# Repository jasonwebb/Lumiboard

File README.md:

## Lumiboard

Lumiboard is an open-source platform for controlling many types of LEDs. An external sensor board enables tons of fun interactivity, and an on-board Bluetooth transceiver let's you control everything via smartphone or tablet. Lumiboard can control all of these types of LEDs:

* Discrete LEDs
* High-power common-cathode RGB (or single-color) LEDs, up to 5W
* Basic LED strips
* Digitally-addressable LED arrays (such as NeoPixel-based packages)
* I2C LED pixels (like the BlinkM)

## Board features
* **ATMega328** with the Arduino Pro Mini (8 mHz @ 3.3V) bootloader flashed
* **Screw terminals** allow all board functions to be easily tapped into.
* **Six PWM pins** broken out and connected through a ULN2003, so you can sink two high-power RGB LEDs.
* **I2C interface** (SDA and SCL pins) for programmable LEDs like the BlinkM. 
* **Three potentiometer inputs** so you can control RGB colors directly, or connect other sensors as analog inputs.
* **External sensor board** containing a temperature sensor, ambient light sensor and sound sensor.
* **Bluetooth transceiver** accessible via SoftwareSerial, so you can easily control your LEDs remotely using your smartphone or tablet.
* **FTDI interface (3.3V)** so you can re-program the board at any time manually.

## More information
* Author website: http://jason-webb.info
* All my blog posts about this project: http://jason-webb.info/tag/lumiboard/
* Wiki: http://jason-webb.info/wiki/index.php?title=Lumiboard

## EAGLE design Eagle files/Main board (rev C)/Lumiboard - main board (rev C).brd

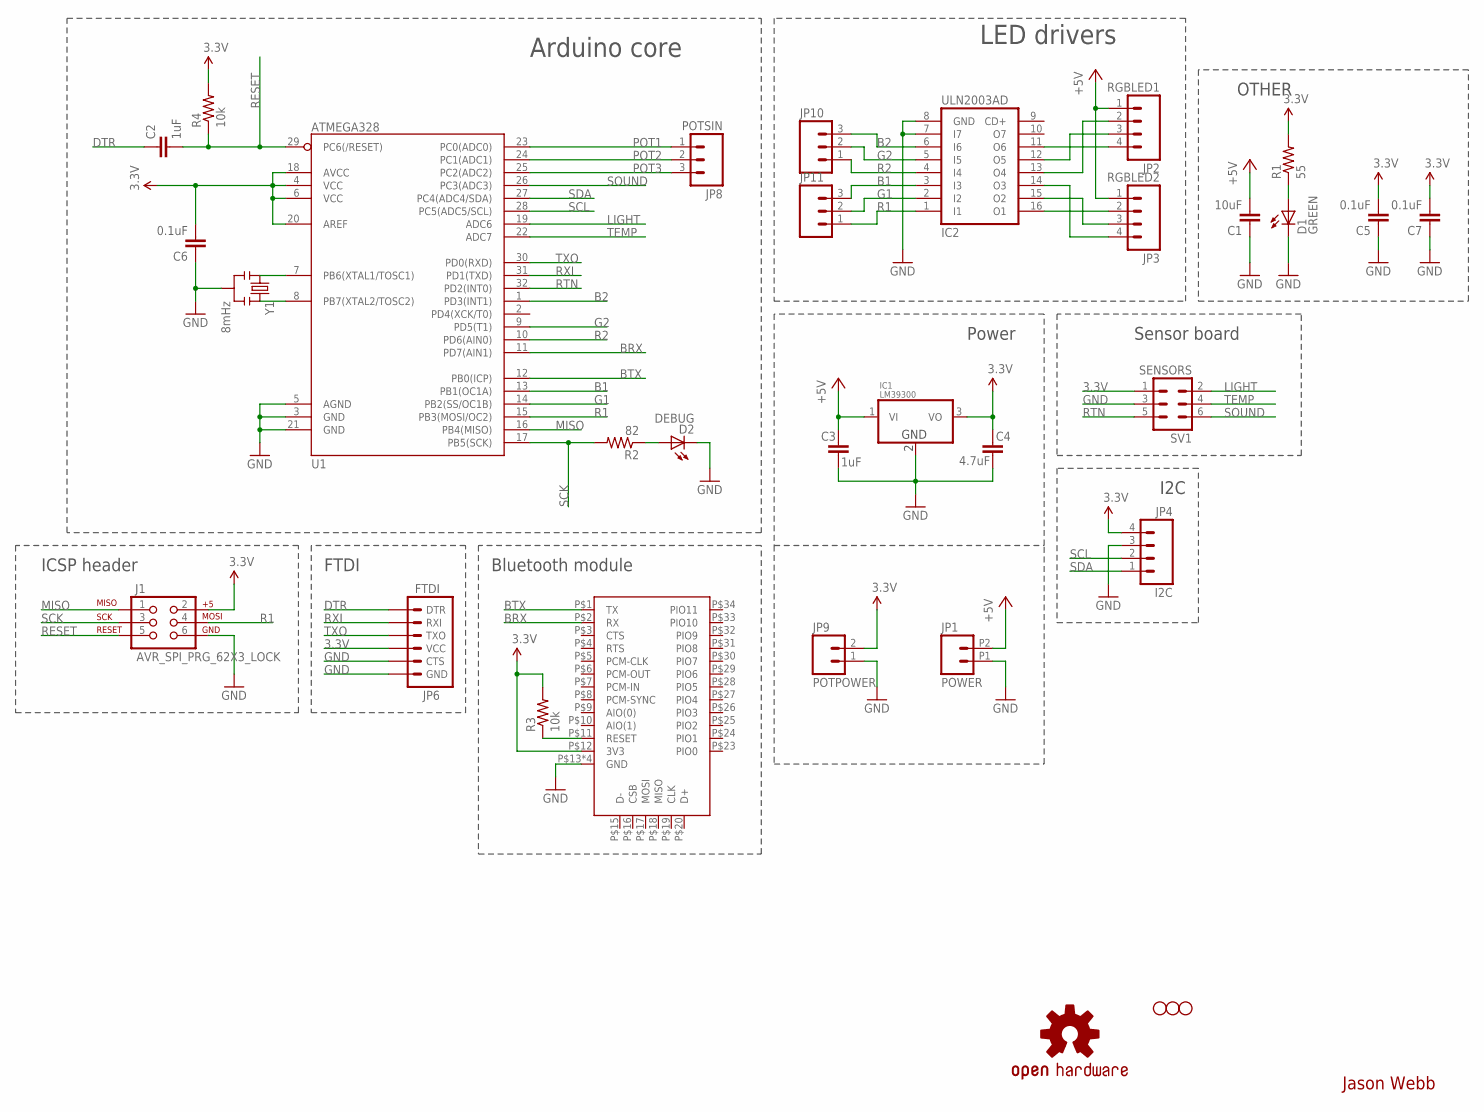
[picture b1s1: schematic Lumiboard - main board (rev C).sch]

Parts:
C1: 10uF; 0805
C2, C3: 1uF; 0805
C4: 4.7uF; 0805
C5, C6, C7: 0.1uF; 0805
D1: GREEN; CHIPLED_0805
D2: DEBUG; CHIPLED_0805
H1, H2, H3: STAND-OFFTIGHT; STAND-OFF-TIGHT
IC1: LM39300; DPAK
IC2: ULN2003AD; SO16
J1: AVR_SPI_PRG_62X3_LOCK; 2X3_LOCK
JP1: POWER; 1X02_2.54_SCREWTERM
JP2: RGBLED1; 1X04
JP3: RGBLED2; 1X04
JP4: I2C; 1X04
JP6: FTDI; 1X06_LOCK
JP8: POTSIN; 1X03
JP9: POTPOWER; 1X02
JP10, JP11: M03PTH; 1X03
LOGO1: OSHW-LOGOS; OSHW-LOGO-S
R1: 55; 0805
R2: 82; 0805
R3, R4: 10k; 0805
SV1: SENSORS; ML6
U1: ATMEGA328; TQFP32-08
U2: DX_BT_MODULE; DXBLUETOOTHMODULE
Y1: 8mHz; RESONATOR-SMD

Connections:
3.3V: C4.2, C5.2, C6.2, C7.2, IC1.3 (VO), J1.2, JP4.4, JP6.4 (VCC), JP9.2, R1.2, R3.2, R4.2, SV1.1, U1.4 (VCC), U1.6 (VCC), U1.18 (AVCC), U1.20 (AREF), U2.P$12 (3V3)
+5V: C1.2, C3.2, IC1.1 (VI), JP1.P2 (2), JP2.1, JP3.1
B1: IC2.3 (I3), JP11.3, U1.13 (PB1(OC1A))
B2: IC2.6 (I6), JP10.3, U1.1 (PD3(INT1))
BRX: U1.11 (PD7(AIN1)), U2.P$2 (RX)
BTRESET: R3.1, U2.P$11 (RESET)
BTX: U1.12 (PB0(ICP)), U2.P$1 (TX)
DTR: C2.1, JP6.1 (DTR)
G1: IC2.2 (I2), JP11.2, U1.14 (PB2(SS/OC1B))
G2: IC2.5 (I5), JP10.2, U1.9 (PD5(T1))
GND: C1.1, C3.1, C4.1, C5.1, C6.1, C7.1, D1.C, D2.C, IC1.2 (GND), IC2.7 (I7), IC2.8 (GND), J1.6, JP1.P1 (1), JP4.3, JP6.5 (CTS), JP6.6 (GND), JP9.1, SV1.3, U1.3 (GND), U1.5 (AGND), U1.21 (GND), U2.P$13 (GND), U2.P$14 (GND), U2.P$21 (GND), U2.P$22 (GND), Y1.2
LIGHT: SV1.2, U1.19 (ADC6)
MISO: J1.1, U1.16 (PB4(MISO))
unnamed: IC2.16 (O1), JP3.2
unnamed: IC2.15 (O2), JP3.3
unnamed: IC2.13 (O4), JP2.2
unnamed: IC2.14 (O3), JP3.4
unnamed: IC2.12 (O5), JP2.3
unnamed: U1.7 (PB6(XTAL1/TOSC1)), Y1.1
unnamed: U1.8 (PB7(XTAL2/TOSC2)), Y1.3
unnamed: D1.A, R1.1
unnamed: IC2.11 (O6), JP2.4
unnamed: D2.A, R2.1
POT1: JP8.1, U1.23 (PC0(ADC0))
POT2: JP8.2, U1.24 (PC1(ADC1))
POT3: JP8.3, U1.25 (PC2(ADC2))
R1: IC2.1 (I1), J1.4, JP11.1, U1.15 (PB3(MOSI/OC2))
R2: IC2.4 (I4), JP10.1, U1.10 (PD6(AIN0))
RESET: C2.2, J1.5, R4.1, U1.29 (PC6(/RESET))
RTN: SV1.5, U1.32 (PD2(INT0))
RXI: JP6.2 (RXI), U1.31 (PD1(TXD))
SCK: J1.3, R2.2, U1.17 (PB5(SCK))
SCL: JP4.2, U1.28 (PC5(ADC5/SCL))
SDA: JP4.1, U1.27 (PC4(ADC4/SDA))
SOUND: SV1.6, U1.26 (PC3(ADC3))
TEMP: SV1.4, U1.22 (ADC7)
TXO: JP6.3 (TXO), U1.30 (PD0(RXD))

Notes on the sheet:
Jason Webb
Arduino core
Bluetooth module
Sensor board
LED drivers
Power
FTDI
I2C
OTHER
ICSP header

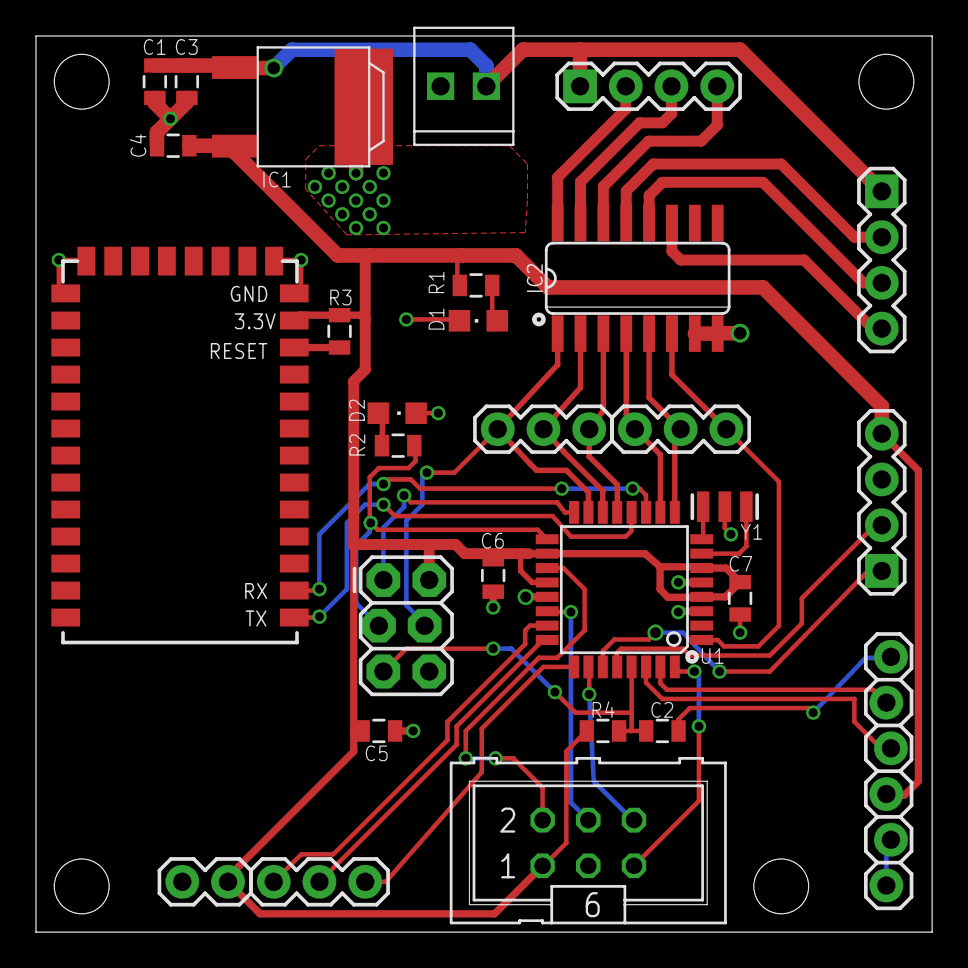
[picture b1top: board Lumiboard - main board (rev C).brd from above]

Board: 4 copper layers, 49.8 x 49.8 mm, 34 parts (1 on the bottom side), 37 nets.

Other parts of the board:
H4: STAND-OFFTIGHT; STAND-OFF-TIGHT

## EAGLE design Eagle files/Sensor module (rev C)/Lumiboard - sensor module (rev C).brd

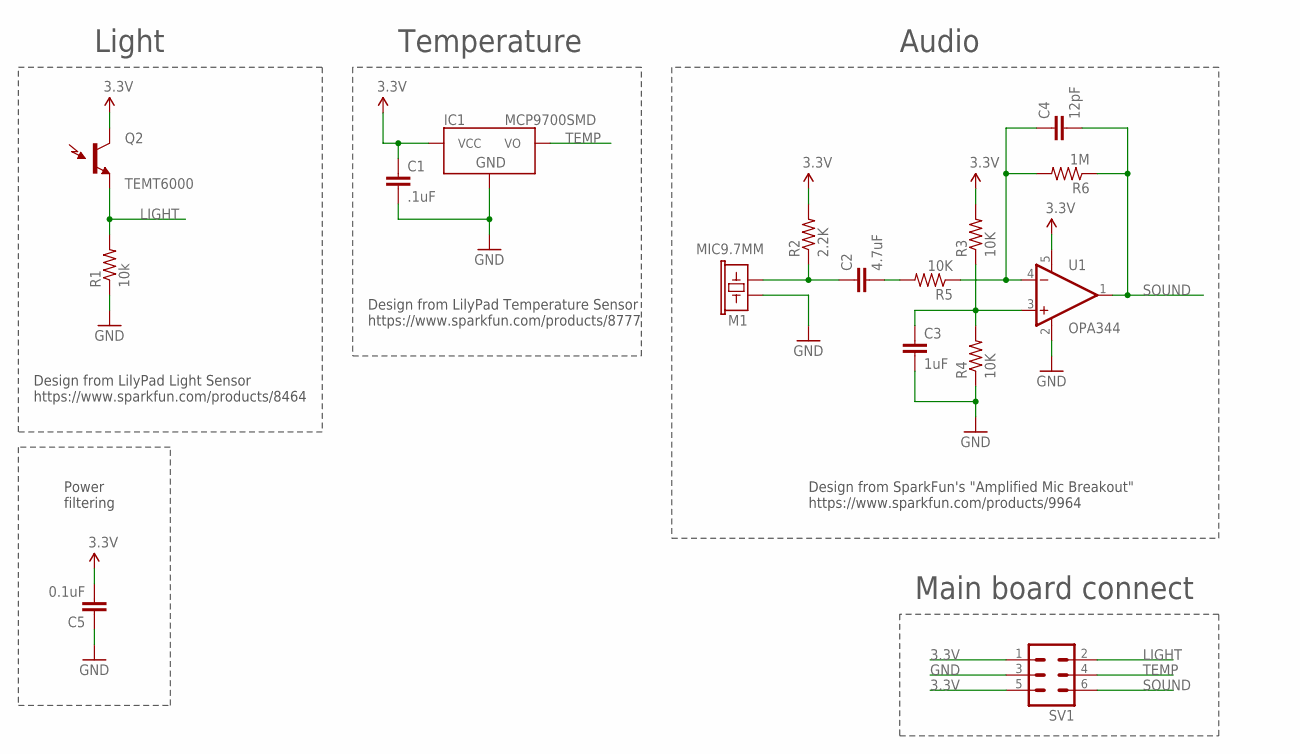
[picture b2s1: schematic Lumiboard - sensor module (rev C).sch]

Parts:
C1: .1uF; 0805
C2: 4.7uF; 0805
C3: 1uF; 0805
C4: 12pF; 0805
C5: 0.1uF; 0805
IC1: MCP9700SMD; SOT23-3
M1: MIC9.7MM; MIC-9.7MM
Q2: TEMT6000; TEMT6000-SEN
R1: 10k; 0805
R2: 2.2K; 0805
R3, R4, R5: 10K; 0805
R6: 1M; 0805
SV1: ML6
U1: OPA344; SOT23-5

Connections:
3.3V: C1.1, C5.2, IC1.1 (VCC), Q2.COLLECTOR (C1), R2.2, R3.2, SV1.1, SV1.5, U1.5 (V+)
GND: C1.2, C3.2, C5.1, IC1.3 (GND), M1.2, R1.1, R4.1, SV1.3, U1.2 (V-)
LIGHT: Q2.EMITTER (E1), R1.2, SV1.2
unnamed: C2.1, M1.1, R2.1
unnamed: C4.1, R5.1, R6.2, U1.4 (-IN)
unnamed: C2.2, R5.2
unnamed: C3.1, R3.1, R4.2, U1.3 (+IN)
SOUND: C4.2, R6.1, SV1.6, U1.1 (OUT)
TEMP: IC1.2 (VO), SV1.4

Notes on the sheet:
Light
Temperature
Main board connect
Audio
Design from SparkFun's "Amplified Mic Breakout" https://www.sparkfun.com/products/9964
Design from LilyPad Temperature Sensor https://www.sparkfun.com/products/8777
Design from LilyPad Light Sensor https://www.sparkfun.com/products/8464
Power filtering

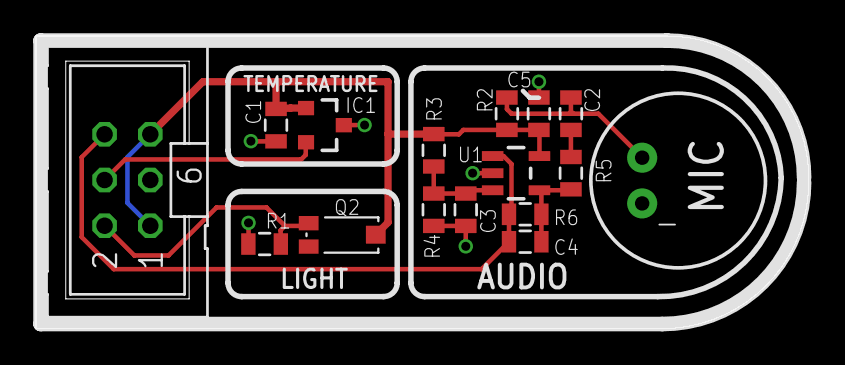
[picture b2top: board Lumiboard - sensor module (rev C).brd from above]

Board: 4 copper layers, 42.9 x 16.3 mm, 16 parts (0 on the bottom side), 9 nets.

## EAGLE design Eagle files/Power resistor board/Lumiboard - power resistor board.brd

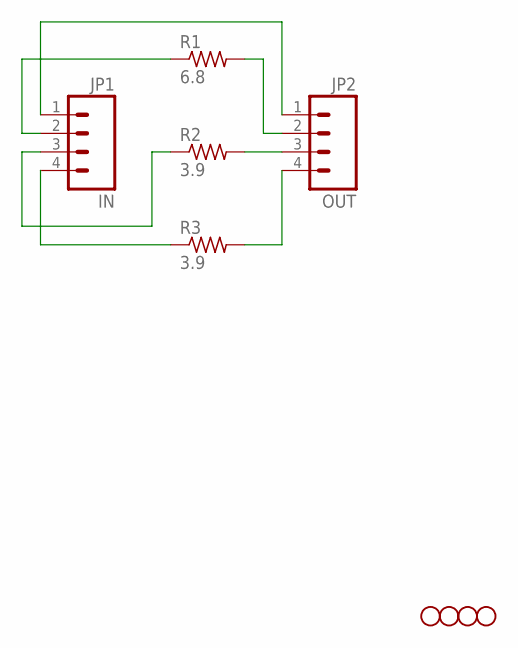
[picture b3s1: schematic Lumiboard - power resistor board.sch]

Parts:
IN: JP1; 1X04
JP1, JP2, JP3, JP4: STAND-OFF
OUT: JP2; 1X04
R1: 6.8; 0411/15
R2, R3: 3.9; 0411/15

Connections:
unnamed: IN.1, OUT.1
unnamed: OUT.3, R2.2
unnamed: IN.4, R3.1
unnamed: OUT.4, R3.2
unnamed: IN.3, R2.1
unnamed: OUT.2, R1.2
unnamed: IN.2, R1.1

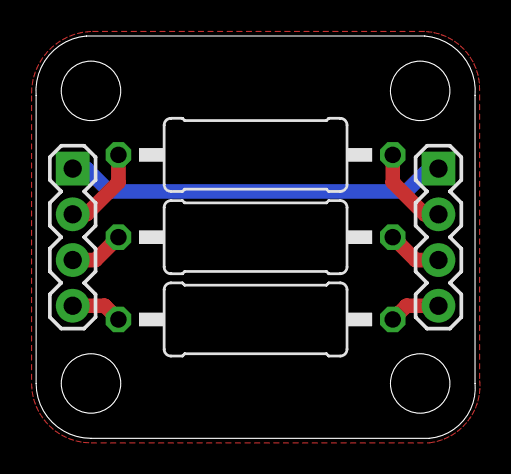
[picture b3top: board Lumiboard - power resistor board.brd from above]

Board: 2 copper layers, 24.4 x 22.4 mm, 9 parts (0 on the bottom side), 7 nets.

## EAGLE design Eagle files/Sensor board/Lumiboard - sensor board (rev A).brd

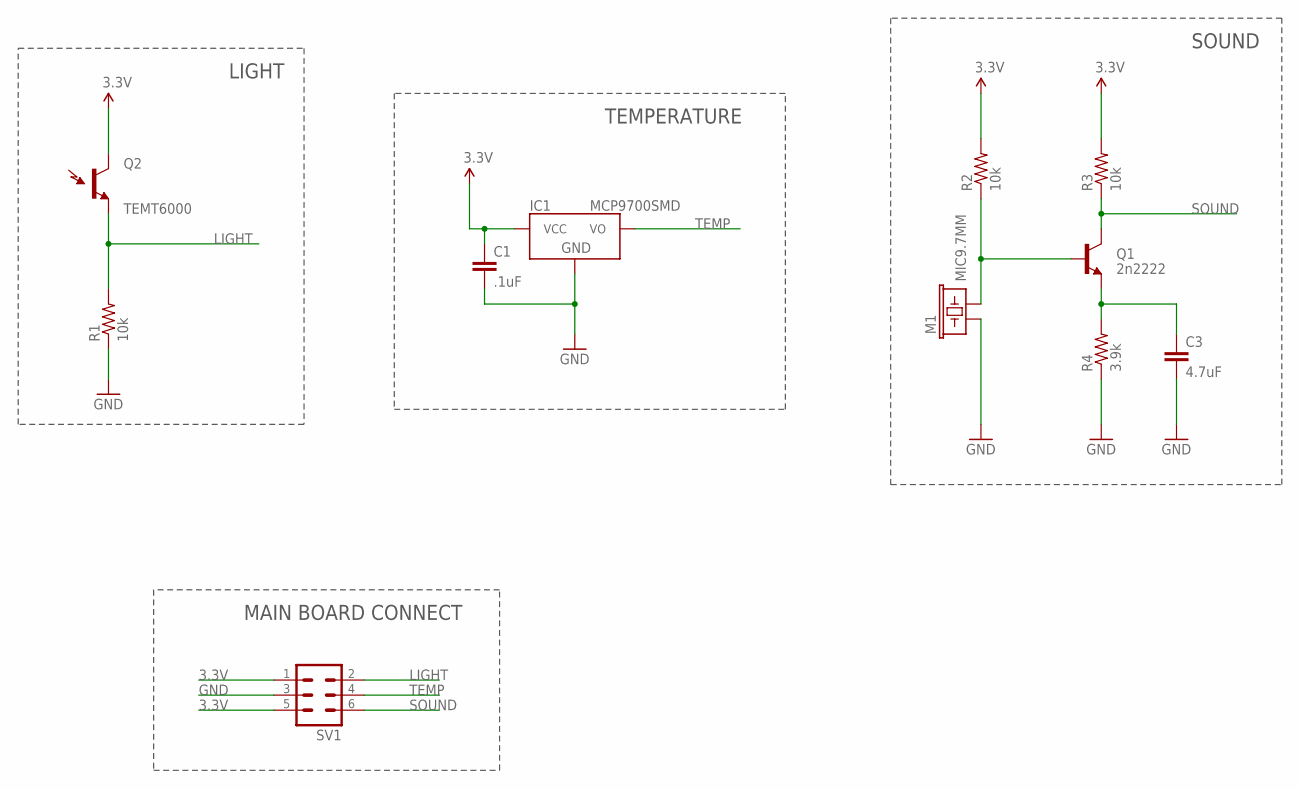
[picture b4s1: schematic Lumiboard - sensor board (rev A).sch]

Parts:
C1: .1uF; 0805
C3: 4.7uF; 0805
IC1: MCP9700SMD; SOT23-3
M1: MIC9.7MM; MIC-9.7MM
Q1: 2n2222; SOT23-3
Q2: TEMT6000; TEMT6000-SEN
R1, R2, R3: 10k; R0805
R4: 3.9k; R0805
SV1: ML6

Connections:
3.3V: C1.1, IC1.1 (VCC), Q2.COLLECTOR (C1), R2.2, R3.2, SV1.1, SV1.5
GND: C1.2, C3.2, IC1.3 (GND), M1.1, R1.1, R4.1, SV1.3
LIGHT: Q2.EMITTER (E1), R1.2, SV1.2
unnamed: M1.2, Q1.1 (B), R2.1
unnamed: C3.1, Q1.2 (E), R4.2
SOUND: Q1.3 (C), R3.1, SV1.6
TEMP: IC1.2 (VO), SV1.4

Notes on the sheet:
LIGHT
TEMPERATURE
SOUND
MAIN BOARD CONNECT

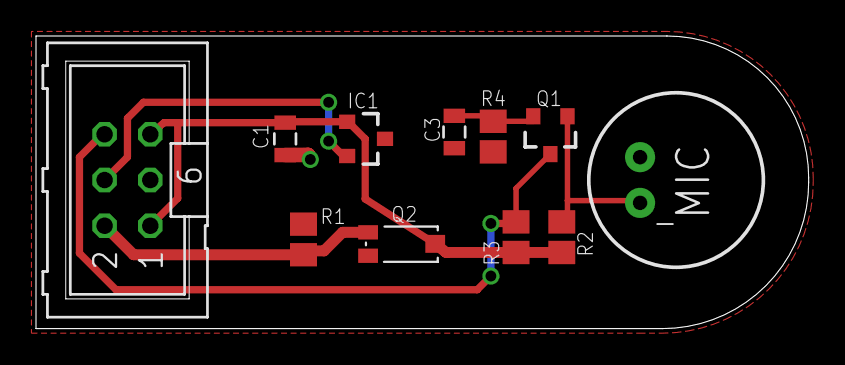
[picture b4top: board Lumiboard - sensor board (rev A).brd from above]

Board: 2 copper layers, 42.9 x 16.3 mm, 11 parts (0 on the bottom side), 7 nets.

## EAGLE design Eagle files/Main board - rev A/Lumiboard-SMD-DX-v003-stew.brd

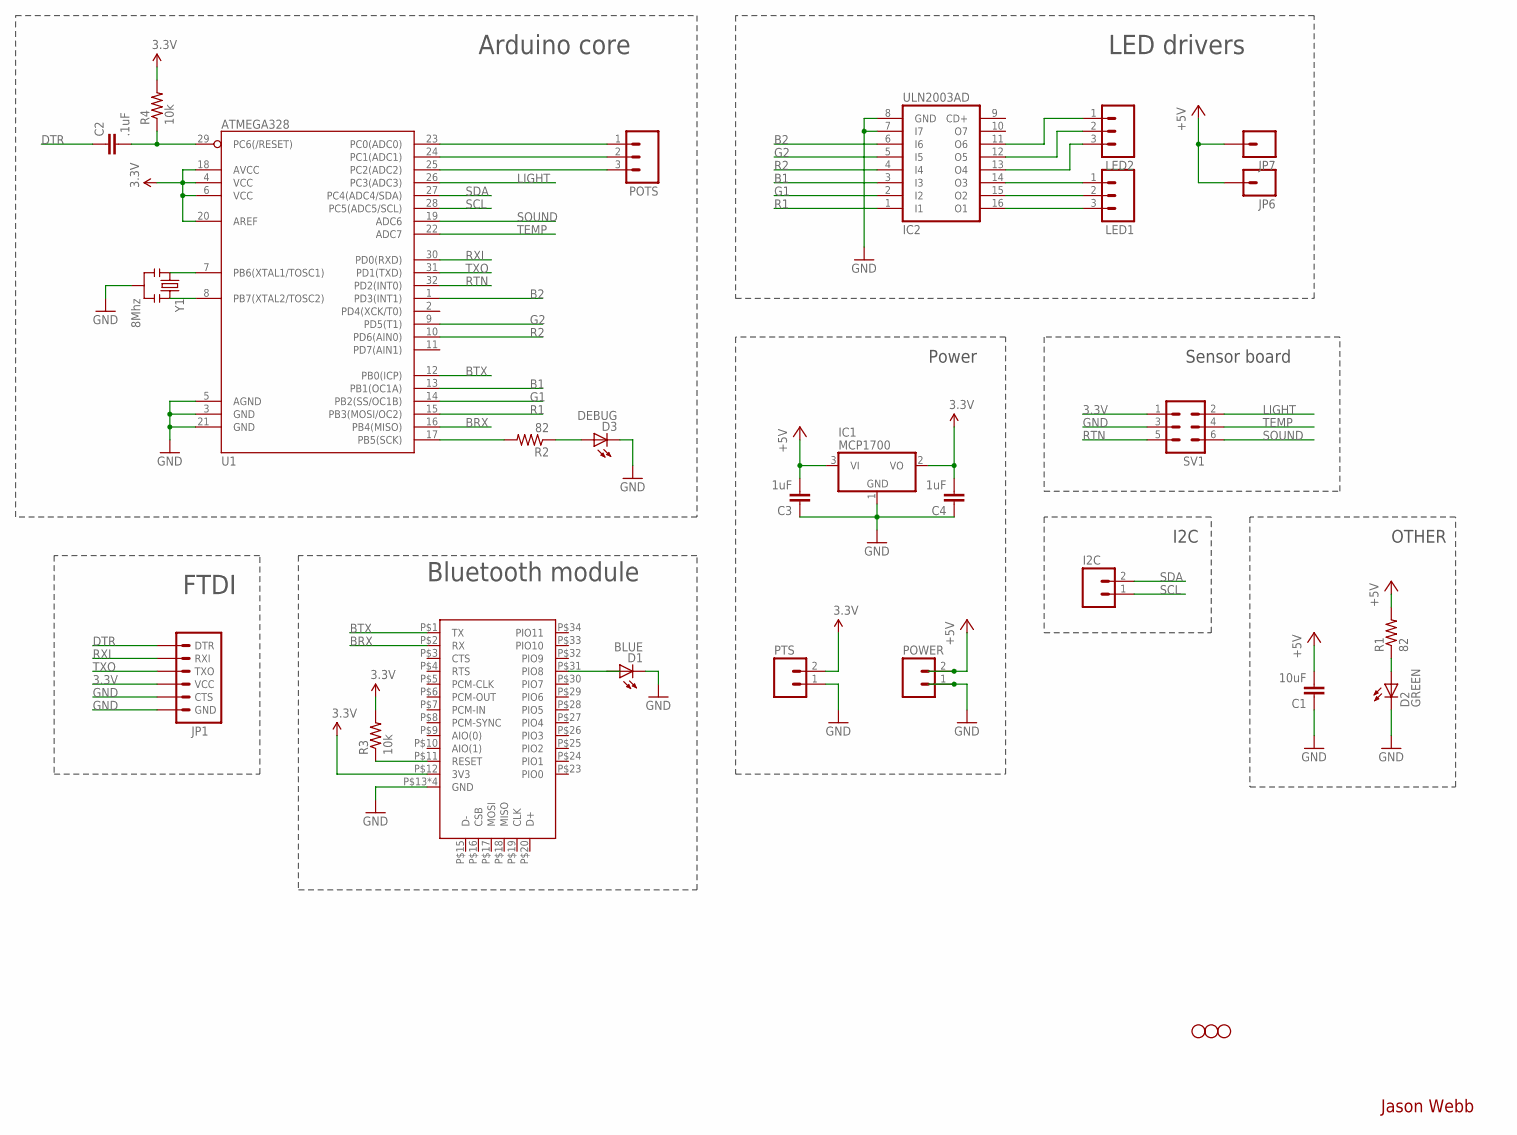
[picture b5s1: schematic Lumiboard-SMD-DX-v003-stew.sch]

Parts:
C1: 10uF; 0805
C2: .1uF; 0805
C3, C4: 1uF; 0805
D1: BLUE; CHIPLED_0805
D2: GREEN; CHIPLED_0805
D3: DEBUG; CHIPLED_0805
I2C: M02PTH; 1X02
IC1: MCP1700; SOT23
IC2: ULN2003AD; SO16
JP1: ARDUINO_SERIAL_PROGRAMLOCK; 1X06_LOCK
JP2, JP4, JP5: STAND-OFFTIGHT; STAND-OFF-TIGHT
JP6, JP7: M01PTH; 1X01
LED1, LED2: M03PTH; 1X03
POTS: M03PTH; 1X03
POWER: M02PTH; 1X02
PTS: M02PTH; 1X02
R1, R2: 82; R0805
R3, R4: 10k; R0805
SV1: ML6
U1: ATMEGA328; TQFP32-08
U2: DX_BT_MODULE; DXBLUETOOTHMODULE
Y1: 8Mhz; RESONATOR-SMD

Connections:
3.3V: C4.2, IC1.2 (VO), JP1.4 (VCC), PTS.2, R3.2, R4.2, SV1.1, U1.4 (VCC), U1.6 (VCC), U1.18 (AVCC), U1.20 (AREF), U2.P$12 (3V3)
+5V: C1.2, C3.2, IC1.3 (VI), JP6.1, JP7.1, POWER.2, R1.2
B1: IC2.3 (I3), U1.13 (PB1(OC1A))
B2: IC2.6 (I6), U1.1 (PD3(INT1))
BRX: U1.16 (PB4(MISO)), U2.P$2 (RX)
BTX: U1.12 (PB0(ICP)), U2.P$1 (TX)
DTR: C2.1, JP1.1 (DTR)
G1: IC2.2 (I2), U1.14 (PB2(SS/OC1B))
G2: IC2.5 (I5), U1.9 (PD5(T1))
GND: C1.1, C3.1, C4.1, D1.C, D2.C, D3.C, IC1.1 (GND), IC2.7 (I7), IC2.8 (GND), JP1.5 (CTS), JP1.6 (GND), POWER.1, PTS.1, SV1.3, U1.3 (GND), U1.5 (AGND), U1.21 (GND), U2.P$13 (GND), U2.P$14 (GND), U2.P$21 (GND), U2.P$22 (GND), Y1.2
LIGHT: SV1.2, U1.26 (PC3(ADC3))
unnamed: IC2.11 (O6), LED2.1
unnamed: D1.A, U2.P$31 (PIO8)
unnamed: IC2.12 (O5), LED2.2
unnamed: R2.2, U1.17 (PB5(SCK))
unnamed: IC2.13 (O4), LED2.3
unnamed: U1.7 (PB6(XTAL1/TOSC1)), Y1.1
unnamed: U1.8 (PB7(XTAL2/TOSC2)), Y1.3
unnamed: D2.A, R1.1
unnamed: C2.2, R4.1, U1.29 (PC6(/RESET))
unnamed: R3.1, U2.P$11 (RESET)
unnamed: POTS.3, U1.25 (PC2(ADC2))
unnamed: D3.A, R2.1
unnamed: IC2.14 (O3), LED1.1
unnamed: IC2.15 (O2), LED1.2
unnamed: IC2.16 (O1), LED1.3
unnamed: POTS.2, U1.24 (PC1(ADC1))
unnamed: POTS.1, U1.23 (PC0(ADC0))
R1: IC2.1 (I1), U1.15 (PB3(MOSI/OC2))
R2: IC2.4 (I4), U1.10 (PD6(AIN0))
RTN: SV1.5, U1.32 (PD2(INT0))
RXI: JP1.2 (RXI), U1.30 (PD0(RXD))
SCL: I2C.1, U1.28 (PC5(ADC5/SCL))
SDA: I2C.2, U1.27 (PC4(ADC4/SDA))
SOUND: SV1.6, U1.19 (ADC6)
TEMP: SV1.4, U1.22 (ADC7)
TXO: JP1.3 (TXO), U1.31 (PD1(TXD))

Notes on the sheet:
Jason Webb
Arduino core
Bluetooth module
Sensor board
LED drivers
Power
FTDI
I2C
OTHER

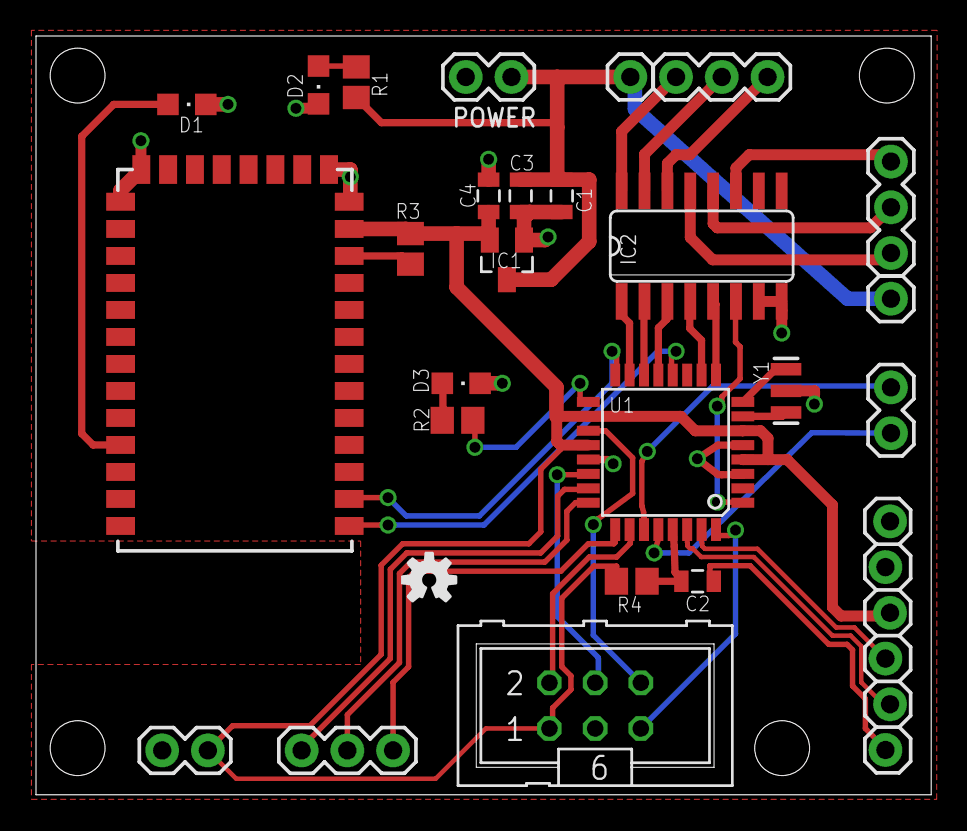
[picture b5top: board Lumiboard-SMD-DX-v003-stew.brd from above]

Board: 2 copper layers, 49.7 x 42.2 mm, 31 parts (0 on the bottom side), 37 nets.

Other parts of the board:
JP3: STAND-OFFTIGHT; STAND-OFF-TIGHT
U$1: OSHW-LOGO-S

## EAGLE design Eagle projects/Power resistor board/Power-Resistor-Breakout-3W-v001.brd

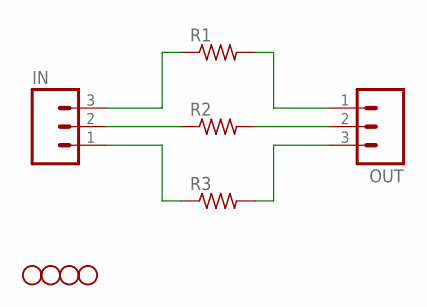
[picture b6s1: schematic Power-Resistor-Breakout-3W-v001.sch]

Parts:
IN: M03PTH; 1X03
JP1, JP2, JP3, JP4: STAND-OFF
OUT: M03PTH; 1X03
R1, R2, R3: R-US_0411/15; 0411/15

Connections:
unnamed: IN.2, R2.1
unnamed: OUT.2, R2.2
unnamed: IN.3, R1.1
unnamed: IN.1, R3.1
unnamed: OUT.3, R3.2
unnamed: OUT.1, R1.2

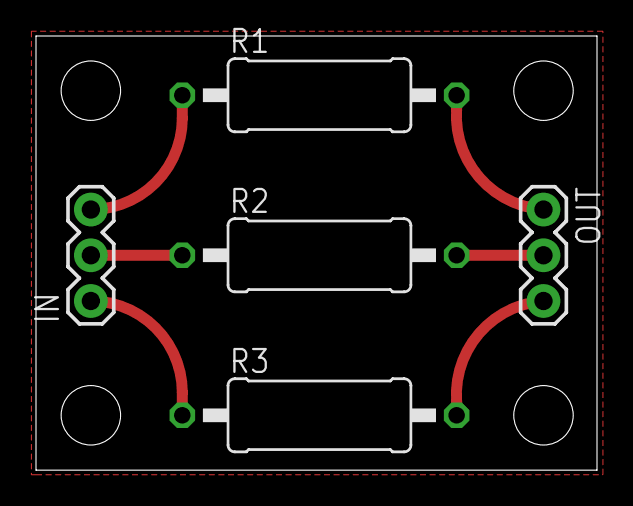
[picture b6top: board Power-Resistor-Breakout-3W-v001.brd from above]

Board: 2 copper layers, 31.2 x 24.1 mm, 9 parts (0 on the bottom side), 6 nets.

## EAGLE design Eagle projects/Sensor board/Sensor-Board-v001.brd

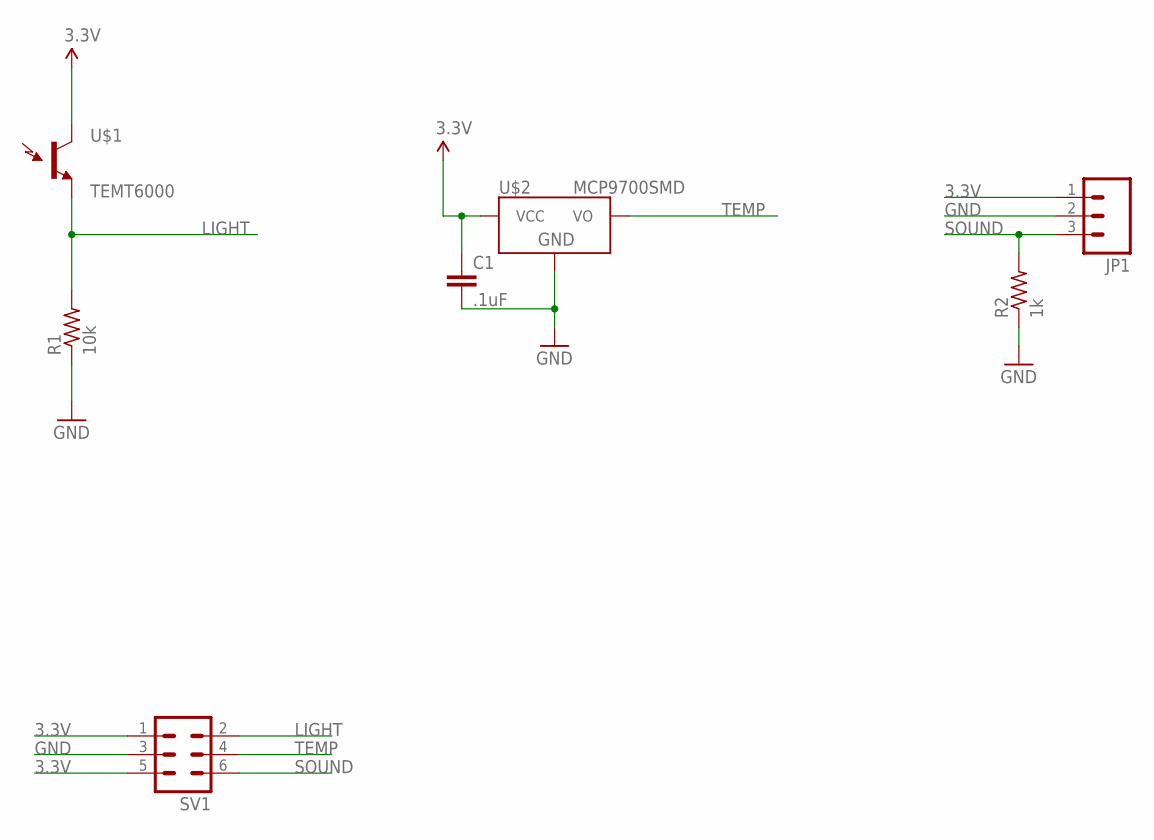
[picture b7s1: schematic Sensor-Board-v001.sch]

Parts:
C1: .1uF; 0603-CAP
JP1: M03PTH; 1X03
R1: 10k; R0603
R2: 1k; R0603
SV1: ML6
U$1: TEMT6000; TEMT6000-SEN
U$2: MCP9700SMD; SOT23-3

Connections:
3.3V: C1.1, JP1.1, SV1.1, SV1.5, U$1.COLLECTOR (C1), U$2.1 (VCC)
GND: C1.2, JP1.2, R1.1, R2.1, SV1.3, U$2.3 (GND)
LIGHT: R1.2, SV1.2, U$1.EMITTER (E1)
SOUND: JP1.3, R2.2, SV1.6
TEMP: SV1.4, U$2.2 (VO)

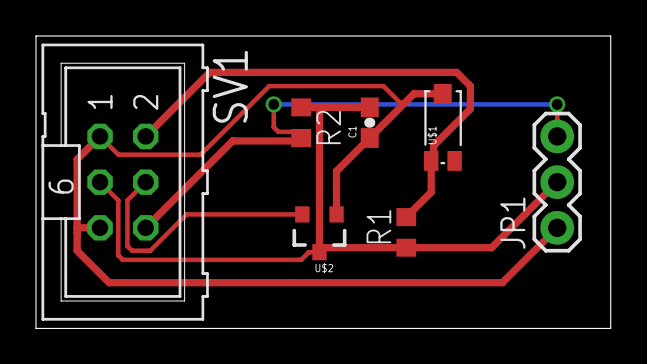
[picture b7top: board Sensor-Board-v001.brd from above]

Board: 2 copper layers, 31.9 x 16.2 mm, 7 parts (0 on the bottom side), 5 nets.

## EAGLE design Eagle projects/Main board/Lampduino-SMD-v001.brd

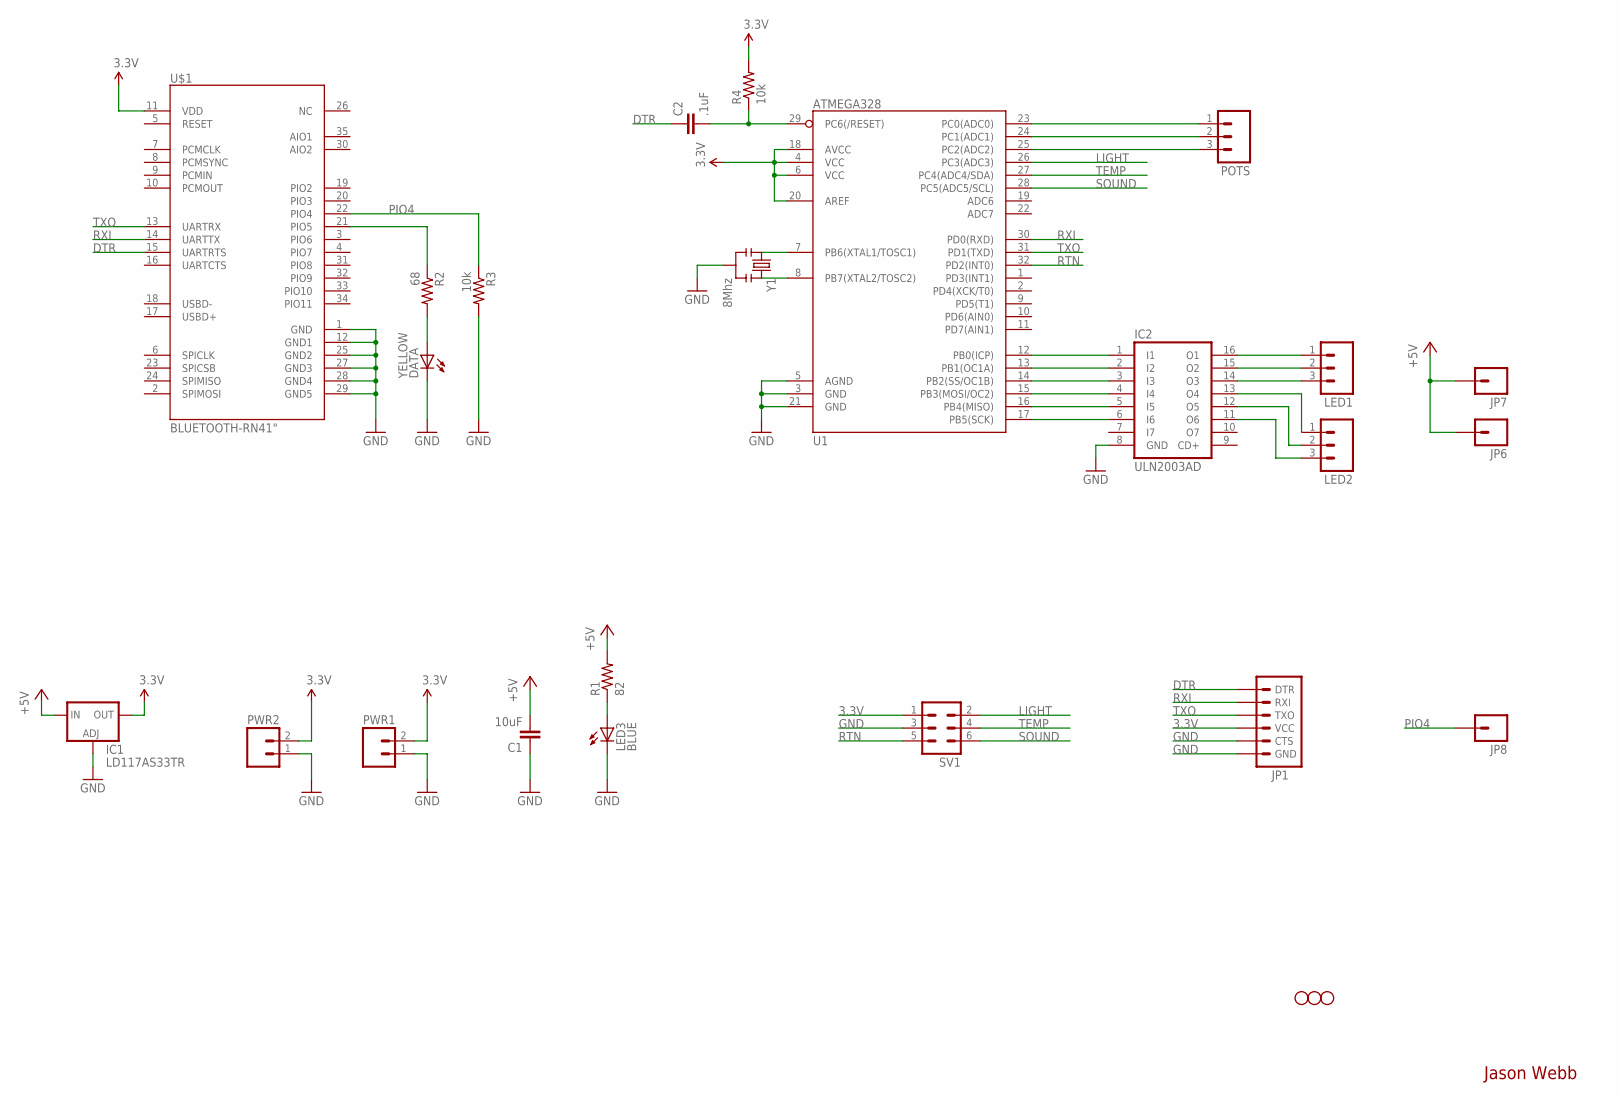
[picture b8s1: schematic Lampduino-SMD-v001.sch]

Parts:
C1: 10uF; 0805
C2: .1uF; 0805
DATA: YELLOW; CHIPLED_0603
IC1: LD117AS33TR; SOT223
IC2: ULN2003AD; SO16
JP1: ARDUINO_SERIAL_PROGRAMLOCK; 1X06_LOCK
JP2, JP4, JP5: STAND-OFFTIGHT; STAND-OFF-TIGHT
JP6, JP7, JP8: M01PTH; 1X01
LED1, LED2: M03PTH; 1X03
LED3: BLUE; CHIPLED_0603
POTS: M03PTH; 1X03
PWR1, PWR2: M02PTH; 1X02
R1: 82; R0603
R2: 68; R0603
R3, R4: 10k; R0603
SV1: ML6
U1: ATMEGA328; TQFP32-08
U$1: BLUETOOTH-RN41"; RN41
Y1: 8Mhz; RESONATOR-SMD

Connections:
3.3V: IC1.4 (OUT), JP1.4 (VCC), PWR1.2, PWR2.2, R4.2, SV1.1, U1.4 (VCC), U1.6 (VCC), U1.18 (AVCC), U1.20 (AREF), U$1.11 (VDD)
+5V: C1.2, IC1.3 (IN), JP6.1, JP7.1, R1.2
DTR: C2.1, JP1.1 (DTR), U$1.15 (UARTRTS)
GND: C1.1, DATA.C, IC1.1 (ADJ), IC2.8 (GND), JP1.5 (CTS), JP1.6 (GND), LED3.C, PWR1.1, PWR2.1, R3.2, SV1.3, U1.3 (GND), U1.5 (AGND), U1.21 (GND), U$1.1 (GND), U$1.12 (GND1), U$1.25 (GND2), U$1.27 (GND3), U$1.28 (GND4), U$1.29 (GND5), Y1.2
LIGHT: SV1.2, U1.26 (PC3(ADC3))
unnamed: IC2.15 (O2), LED1.2
unnamed: IC2.4 (I4), U1.15 (PB3(MOSI/OC2))
unnamed: IC2.14 (O3), LED1.3
unnamed: IC2.5 (I5), U1.16 (PB4(MISO))
unnamed: IC2.16 (O1), LED1.1
unnamed: IC2.6 (I6), U1.17 (PB5(SCK))
unnamed: U1.7 (PB6(XTAL1/TOSC1)), Y1.1
unnamed: U1.8 (PB7(XTAL2/TOSC2)), Y1.3
unnamed: LED3.A, R1.1
unnamed: C2.2, R4.1, U1.29 (PC6(/RESET))
unnamed: R2.1, U$1.21 (PIO5)
unnamed: POTS.3, U1.25 (PC2(ADC2))
unnamed: IC2.1 (I1), U1.12 (PB0(ICP))
unnamed: IC2.2 (I2), U1.13 (PB1(OC1A))
unnamed: IC2.3 (I3), U1.14 (PB2(SS/OC1B))
unnamed: DATA.A, R2.2
unnamed: IC2.13 (O4), LED2.1
unnamed: IC2.12 (O5), LED2.2
unnamed: IC2.11 (O6), LED2.3
unnamed: POTS.2, U1.24 (PC1(ADC1))
unnamed: POTS.1, U1.23 (PC0(ADC0))
PIO4: JP8.1, R3.1, U$1.22 (PIO4)
RTN: SV1.5, U1.32 (PD2(INT0))
RXI: JP1.2 (RXI), U1.30 (PD0(RXD)), U$1.14 (UARTTX)
SOUND: SV1.6, U1.28 (PC5(ADC5/SCL))
TEMP: SV1.4, U1.27 (PC4(ADC4/SDA))
TXO: JP1.3 (TXO), U1.31 (PD1(TXD)), U$1.13 (UARTRX)

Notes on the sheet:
Jason Webb

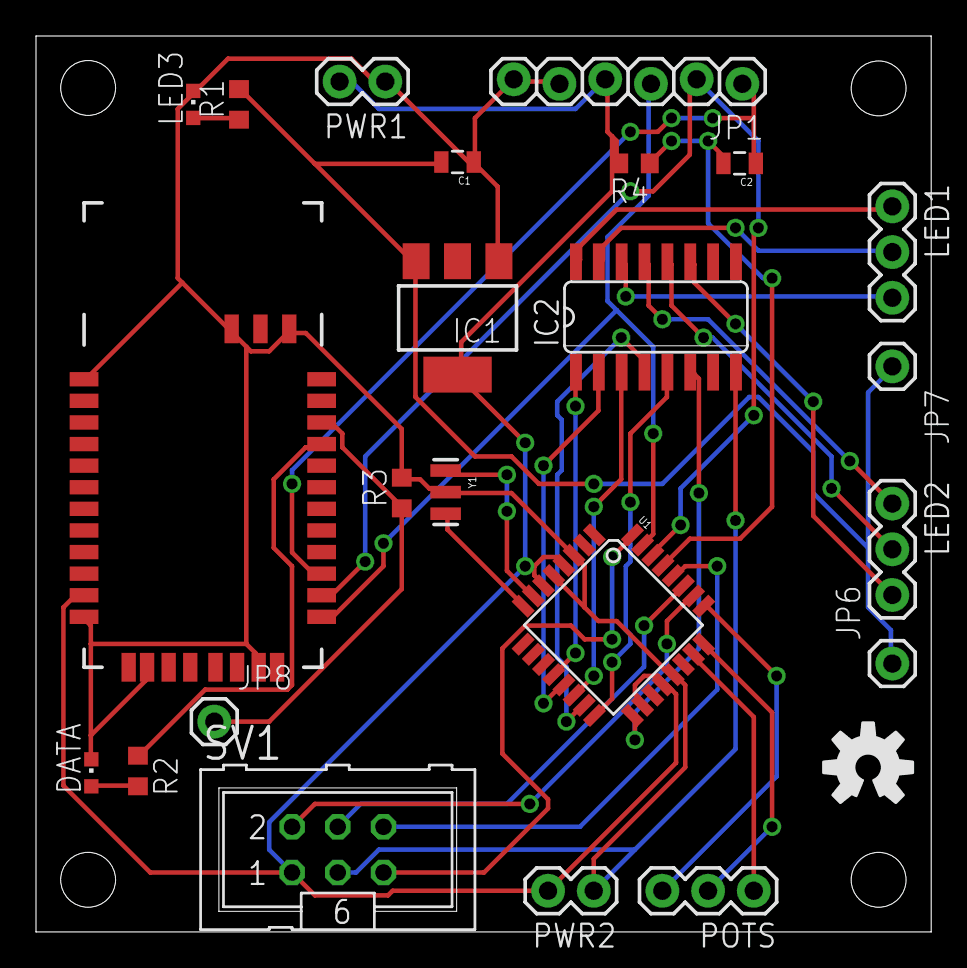
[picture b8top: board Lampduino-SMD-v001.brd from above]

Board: 2 copper layers, 49.7 x 49.8 mm, 28 parts (0 on the bottom side), 32 nets.

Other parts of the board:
JP3: STAND-OFFTIGHT; STAND-OFF-TIGHT
U$2: OSHW-LOGO-M

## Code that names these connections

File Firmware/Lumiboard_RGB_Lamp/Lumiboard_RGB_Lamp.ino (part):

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#define  BT_RX  7
#define  BT_TX  8

#define  POT1  A0
#define  POT2  A1
#define  POT3  A2
#define  POT_THRESHOLD  2

#define  SENSOR_RTN  2
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const byte COLOR_WASH_MODE = 0;    // Color washing (blending between all RGB values)
const byte DIRECT_POT_MODE = 1;    // RGB pots directly control LEDs
const byte THERMOMETER_MODE = 2;   // Red = hot, blue = cold
const byte NIGHTLIGHT_MODE = 3;    // Brightness inversely proportional to ambient light
byte INPUT_MODE = DIRECT_POT_MODE;

void setup() {  
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
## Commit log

2011-12-18 Initial commit of Eagle project files
2012-12-16 Eagle files, Gerber files, new readme
2012-12-16 Removed old folder
2012-12-16 Readme changes
2012-12-16 Readme fixing
2012-12-17 Readme testing
2013-01-01 New Eagle files
2013-01-01 Added BOMs
2013-11-24 New BOM, board files and readme
2013-11-24 readme update
2014-02-09 Initial firmware and sensor module (rev B)
2014-02-09 Removed tmp files
2014-02-28 Updated schematics and BOMs

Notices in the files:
parts and their libraries:
SparkFun-Connectors: Licensing: CC v3.0 Share-Alike You are welcome to use this library for commercial purposes.
